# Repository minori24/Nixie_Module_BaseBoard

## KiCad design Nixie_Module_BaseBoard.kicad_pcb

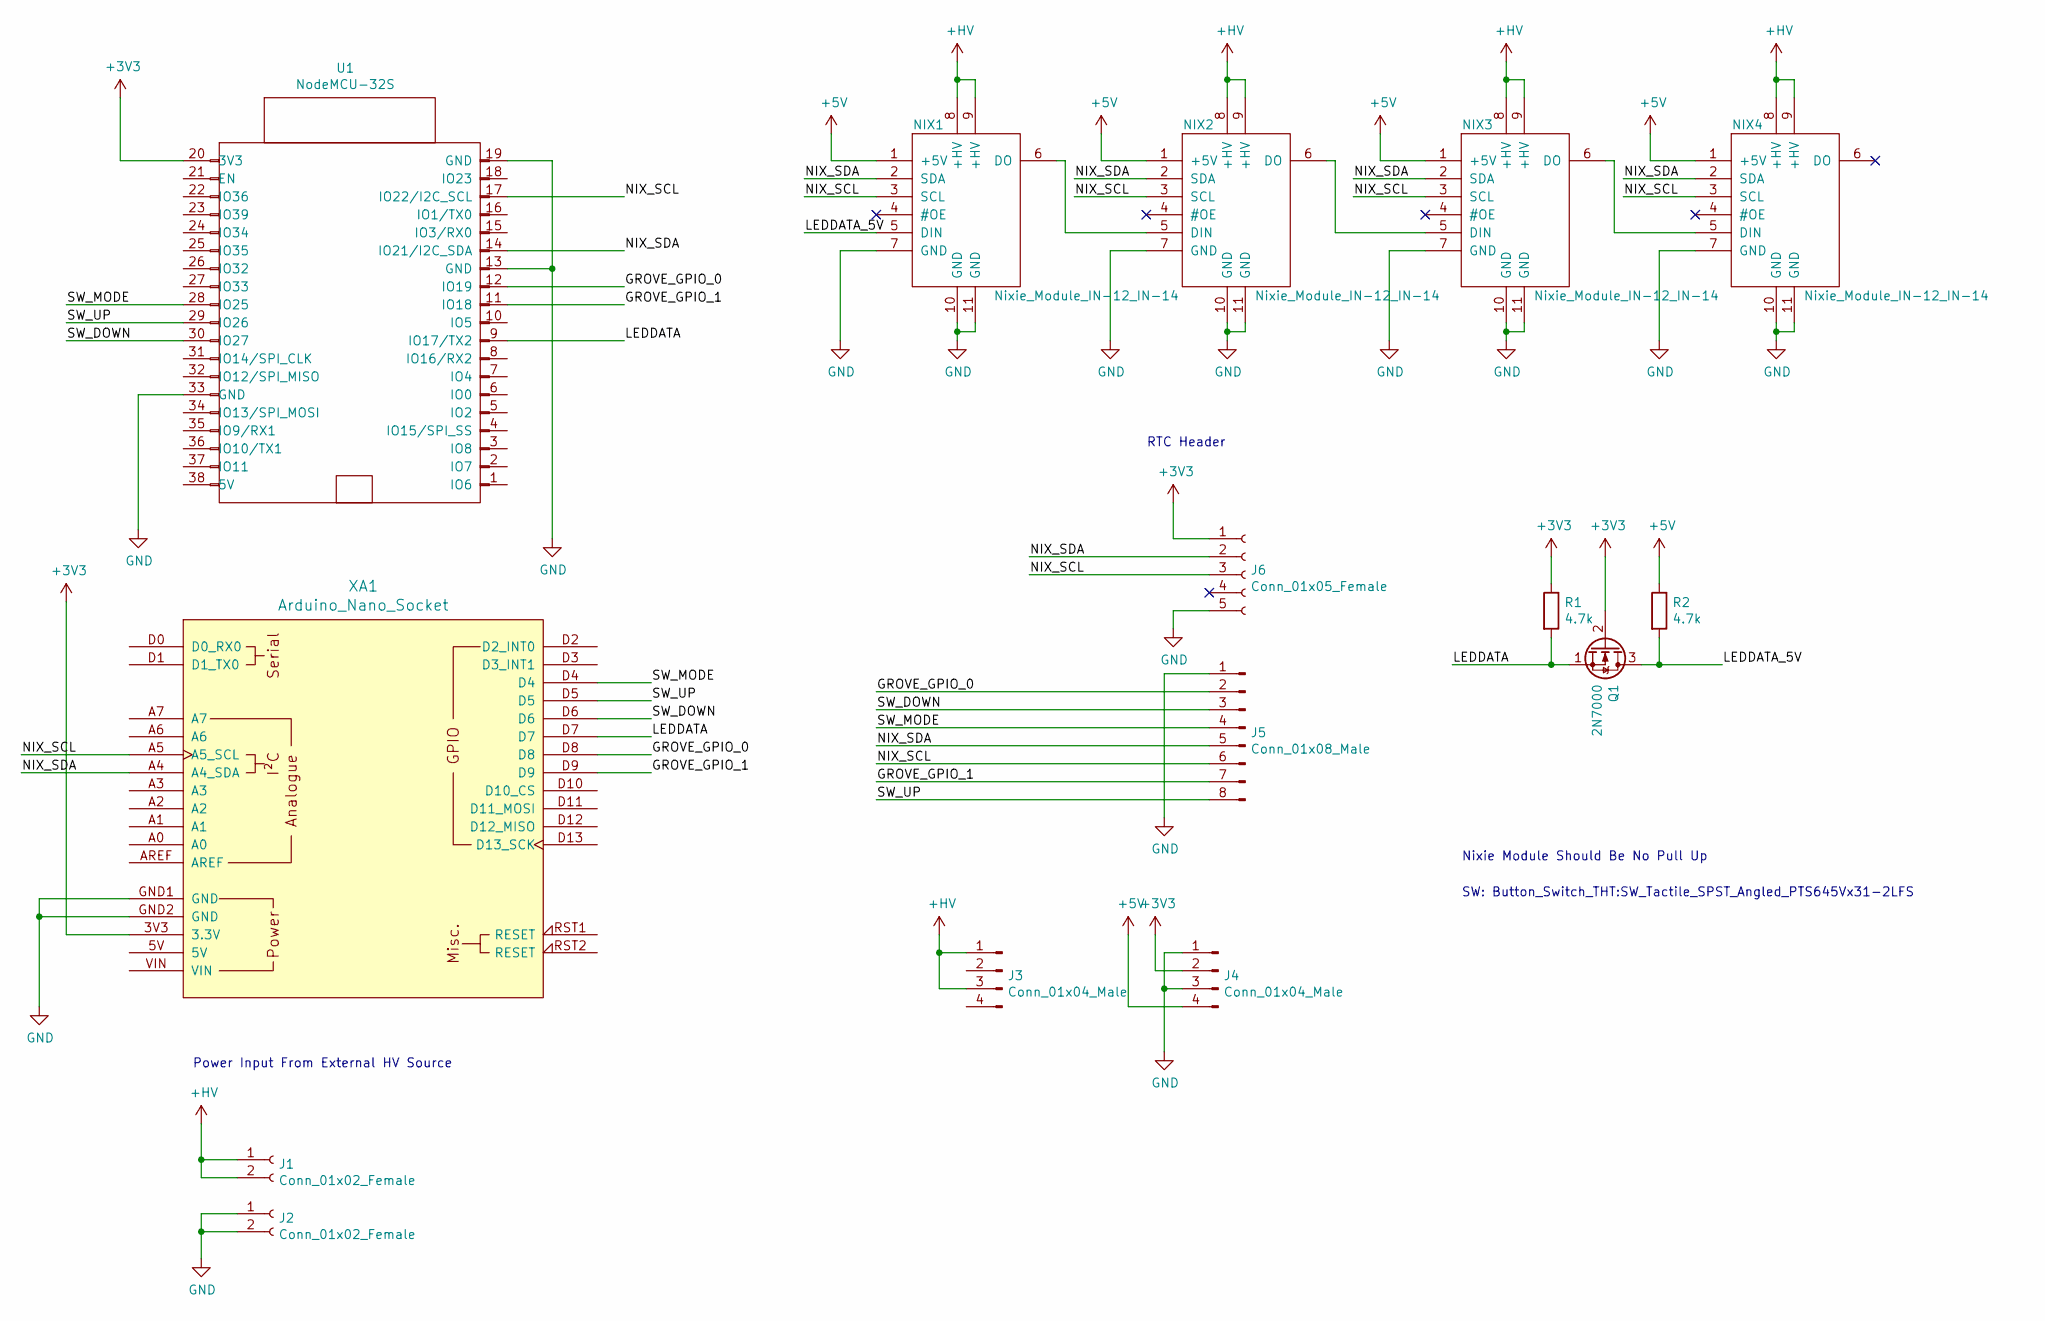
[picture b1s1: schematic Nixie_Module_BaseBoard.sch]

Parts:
J1, J2: Conn_01x02_Female; PinSocket_1x02_P2.54mm_Vertical
J3, J4: Conn_01x04_Male; PinSocket_2x02_P2.54mm_Horizontal
J5: Conn_01x08_Male; PinSocket_2x04_P2.54mm_Horizontal
J6: Conn_01x05_Female; PinSocket_1x05_P2.54mm_Vertical
NIX1, NIX2, NIX3, NIX4: Nixie_Module_IN-12_IN-14; NixieModule
Q1: 2N7000; TO-92_Wide
R1, R2: 4.7k; R_Axial_DIN0207_L6.3mm_D2.5mm_P7.62mm_Horizontal
U1: NodeMCU-32S
XA1: Arduino_Nano_Socket

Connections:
+3V3: J4.2, J6.1, Q1.2 (G), R1.1, U1.20 (3V3), XA1.3V3 (3.3V)
+5V: J4.4, NIX1.1 (+5V), NIX2.1 (+5V), NIX3.1 (+5V), NIX4.1 (+5V), R2.1
+HV: J1.1, J1.2, J3.1, J3.3, NIX1.8 (+HV), NIX1.9 (+HV), NIX2.8 (+HV), NIX2.9 (+HV), NIX3.8 (+HV), NIX3.9 (+HV), NIX4.8 (+HV), NIX4.9 (+HV)
/GROVE_GPIO_0: J5.2, U1.12 (IO19), XA1.D8
/GROVE_GPIO_1: J5.7, U1.11 (IO18), XA1.D9
/LEDDATA: Q1.1 (S), R1.2, U1.9 (IO17/TX2), XA1.D7
/LEDDATA_5V: NIX1.5 (DIN), Q1.3 (D), R2.2
/NIX_SCL: J5.6, J6.3, NIX1.3 (SCL), NIX2.3 (SCL), NIX3.3 (SCL), NIX4.3 (SCL), U1.17 (IO22/I2C_SCL), XA1.A5 (A5_SCL)
/NIX_SDA: J5.5, J6.2, NIX1.2 (SDA), NIX2.2 (SDA), NIX3.2 (SDA), NIX4.2 (SDA), U1.14 (IO21/I2C_SDA), XA1.A4 (A4_SDA)
/SW_DOWN: J5.3, U1.30 (IO27), XA1.D6
/SW_MODE: J5.4, U1.28 (IO25), XA1.D4
/SW_UP: J5.8, U1.29 (IO26), XA1.D5
GND: J2.1, J2.2, J4.1, J4.3, J5.1, J6.5, NIX1.7 (GND), NIX1.10 (GND), NIX1.11 (GND), NIX2.7 (GND), NIX2.10 (GND), NIX2.11 (GND), NIX3.7 (GND), NIX3.10 (GND), NIX3.11 (GND), NIX4.7 (GND), NIX4.10 (GND), NIX4.11 (GND), U1.13 (GND), U1.19 (GND), U1.33 (GND), XA1.GND1 (GND), XA1.GND2 (GND)
unnamed: NIX1.6 (DO), NIX2.5 (DIN)
unnamed: NIX2.6 (DO), NIX3.5 (DIN)
unnamed: NIX3.6 (DO), NIX4.5 (DIN)

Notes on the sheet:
Nixie Module Should Be No Pull Up
SW: Button_Switch_THT:SW_Tactile_SPST_Angled_PTS645Vx31-2LFS
Power Input From External HV Source
RTC Header

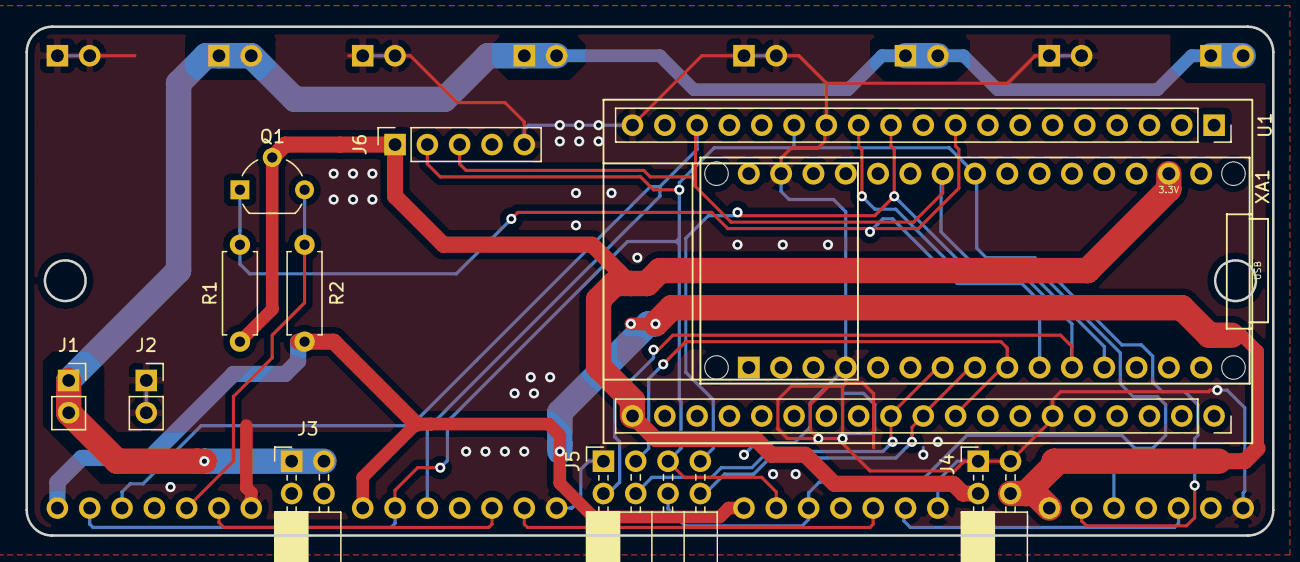
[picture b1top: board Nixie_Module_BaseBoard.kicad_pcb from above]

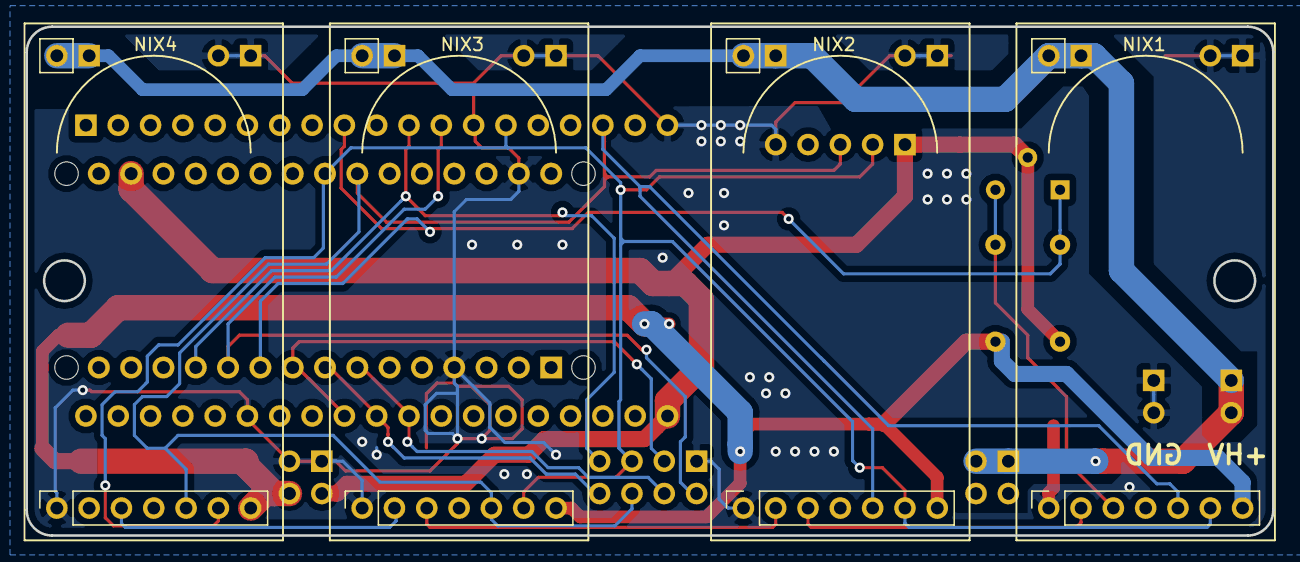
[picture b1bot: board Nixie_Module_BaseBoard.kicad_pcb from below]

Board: 2 copper layers, 98.0 x 40.0 mm, 15 parts (4 on the bottom side), 16 nets.

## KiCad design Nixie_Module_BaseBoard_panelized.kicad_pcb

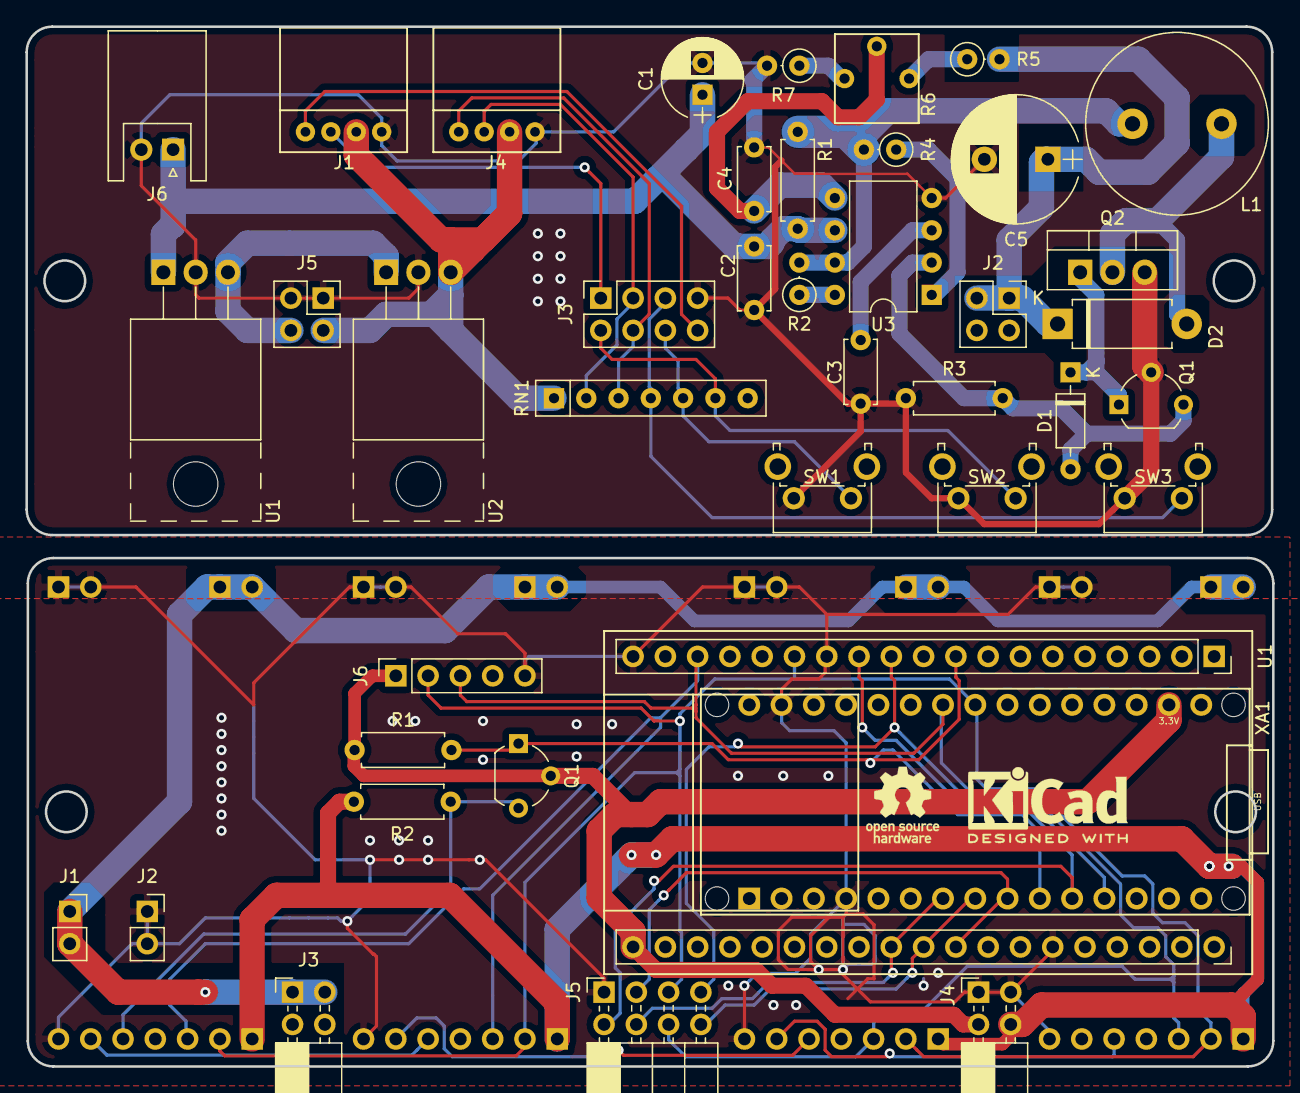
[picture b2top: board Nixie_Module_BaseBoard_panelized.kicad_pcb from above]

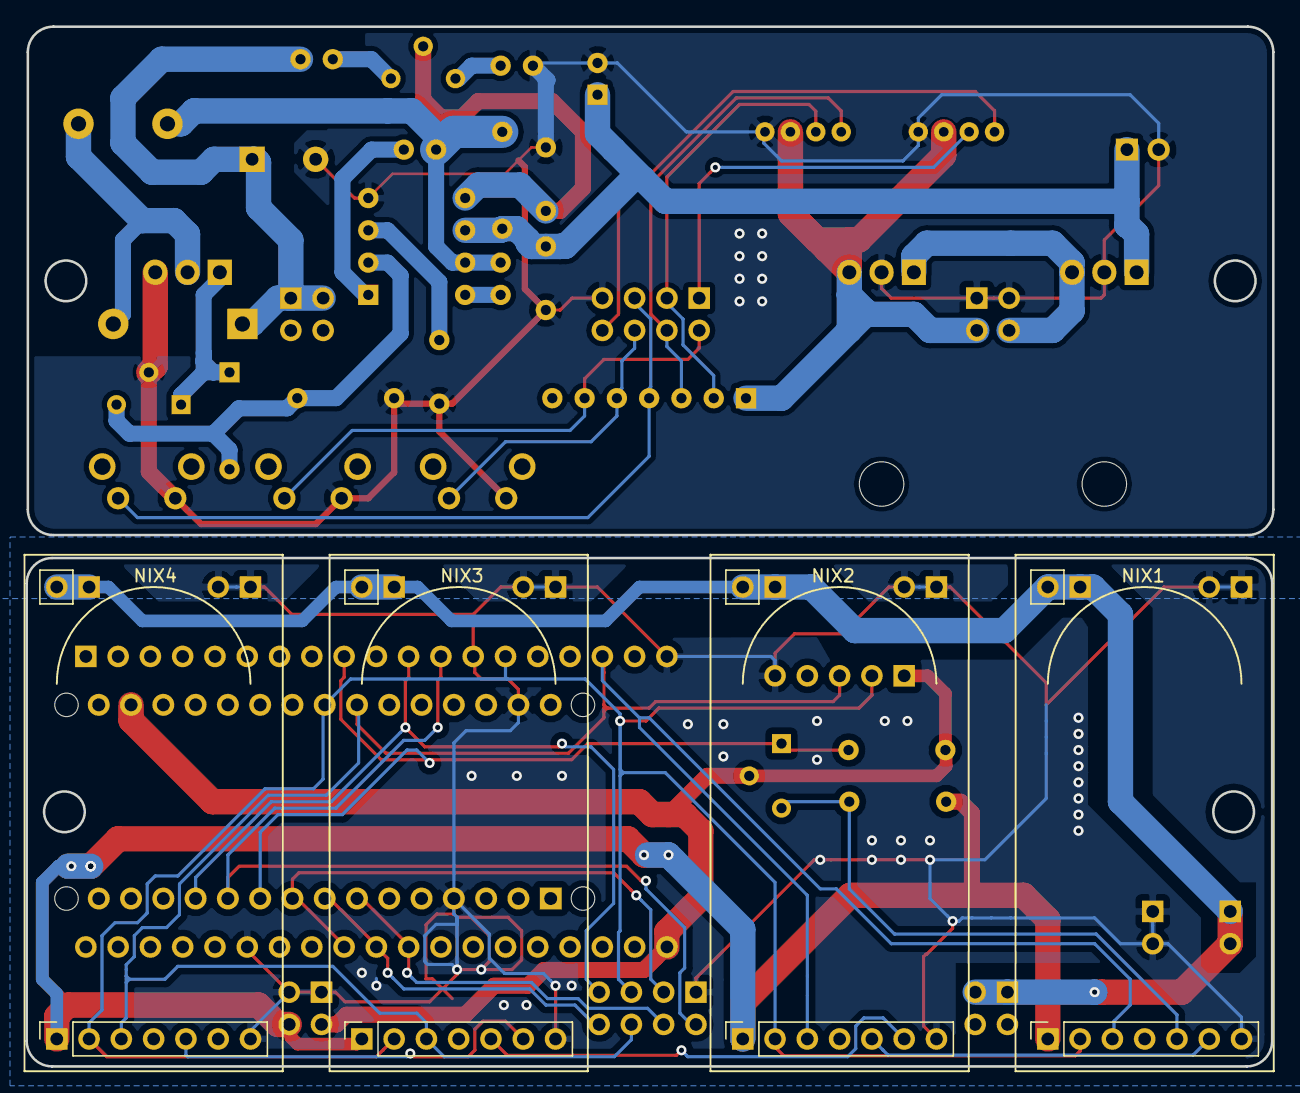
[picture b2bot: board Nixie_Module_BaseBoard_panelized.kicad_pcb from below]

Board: 2 copper layers, 98.1 x 81.8 mm, 45 parts (4 on the bottom side), 27 nets.

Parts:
C1: 100uF_16V; CP_Radial_D6.3mm_P2.50mm
C2, C4: 0.1uF; C_Disc_D5.0mm_W2.5mm_P5.00mm
C3: 1000pF; C_Disc_D5.0mm_W2.5mm_P5.00mm
C5: 4.7u_400V; CP_Radial_D10.0mm_P5.00mm
D1: 1N4148; D_DO-35_SOD27_P7.62mm_Horizontal
D2: UF2010; D_DO-15_P10.16mm_Horizontal
J1, J2: Conn_01x02_Female; PinSocket_1x02_P2.54mm_Vertical
J1#2: Grove_GPIO; Grove_THT
J2#2, J5#2: Conn_01x04_Female; PinSocket_2x02_P2.54mm_Vertical
J3, J4: Conn_01x04_Male; PinSocket_2x02_P2.54mm_Horizontal
J3#2: Conn_01x08_Female; PinSocket_2x04_P2.54mm_Vertical
J4#2: Grove_Analog; Grove_THT
J5: Conn_01x08_Male; PinSocket_2x04_P2.54mm_Horizontal
J6: Conn_01x05_Female; PinSocket_1x05_P2.54mm_Vertical
J6#2: Conn_01x02_Female; JST_XH_S02B-XH-A_02x2.50mm_Angled
L1: 470uH; Inductors_LHL13NB471K
NIX1, NIX2, NIX3, NIX4: Nixie_Module_IN-12_IN-14; NixieModule
Q1: Q_NMOS_SGD; TO-92_Wide
Q1#2: 2SA1015; TO-92_Wide
Q2: 2SK3115; TO-220-3_Vertical
R1, R2: 4.7k; R_Axial_DIN0207_L6.3mm_D2.5mm_P7.62mm_Horizontal
R1#2: 0.15; R_Axial_DIN0207_L6.3mm_D2.5mm_P7.62mm_Horizontal
R2#2: 680; R_Axial_DIN0207_L6.3mm_D2.5mm_P2.54mm_Vertical
R3: 1k; R_Axial_DIN0207_L6.3mm_D2.5mm_P7.62mm_Horizontal
R4: 1k; R_Axial_DIN0207_L6.3mm_D2.5mm_P2.54mm_Vertical
R5: 470k; R_Axial_DIN0207_L6.3mm_D2.5mm_P2.54mm_Vertical
R6: VR_2K; VOL_3362P-1-202LF
R7: 2.2k; R_Axial_DIN0207_L6.3mm_D2.5mm_P2.54mm_Vertical
RN1: R_Network06; R_Array_SIP7
SW1, SW2, SW3: SW_Push; SW_Tactile_SPST_Angled_PTS645Vx31-2LFS
U1: NodeMCU-32S
U1#2, U2: NJM7805S; TO-220-3_Horizontal_TabUp
U3: MC34063A; DIP-8_W7.62mm
XA1: Arduino_Nano_Socket

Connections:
+3V3: J1#2.3, J4.2, J4#2.3, J5#2.3, J6.1, Q1.2, R1.1, RN1.1, U1.20, U2.3, XA1.3V3
+5V: J4.4, J5#2.4, NIX1.1, NIX2.1, NIX3.1, NIX4.1, R2.1, U1#2.3, U2.1
+12V: C1.1, C2.1, J6#2.1, R1#2.2, U1#2.1, U3.6
+HV: C5.1, D2.1, J1.1, J1.2, J2#2.1, J2#2.2, J3.1, J3.3, NIX1.8, NIX1.9, NIX2.8, NIX2.9, NIX3.8, NIX3.9, NIX4.8, NIX4.9, R5.2
/GROVE_GPIO_0: J1#2.1, J3#2.8, J5.2, U1.12, XA1.D8
/GROVE_GPIO_1: J1#2.2, J3#2.1, J5.7, U1.11, XA1.D9
/LEDDATA: Q1.1, R1.2, U1.9, XA1.D7
/LEDDATA_5V: NIX1.5, Q1.3, R2.2
/NIX_SCL: J3#2.4, J4#2.1, J5.6, J6.3, NIX1.3, NIX2.3, NIX3.3, NIX4.3, RN1.3, U1.17, XA1.A5
/NIX_SDA: J3#2.3, J4#2.2, J5.5, J6.2, NIX1.2, NIX2.2, NIX3.2, NIX4.2, RN1.2, U1.14, XA1.A4
/SW_DOWN: J3#2.5, J5.3, RN1.4, SW3.1, U1.30, XA1.D6
/SW_MODE: J3#2.6, J5.4, RN1.5, SW1.1, U1.28, XA1.D4
/SW_UP: J3#2.2, J5.8, RN1.6, SW2.1, U1.29, XA1.D5
GND: C1.2, C2.2, C3.2, C4.2, C5.2, J1#2.4, J2.1, J2.2, J3#2.7, J4.1, J4.3, J4#2.4, J5.1, J5#2.1, J5#2.2, J6.5, J6#2.2, NIX1.7, NIX1.10, NIX1.11, NIX2.7, NIX2.10, NIX2.11, NIX3.7, NIX3.10, NIX3.11, NIX4.7, NIX4.10, NIX4.11, Q1#2.2, Q2.3, R3.1, R7.2, SW1.2, SW2.2, SW3.2, U1.13, U1.19, U1.33, U1#2.2, U2.2, U3.4, XA1.GND1, XA1.GND2
unnamed: C3.1, U3.3
unnamed: C4.1, R6.2, U3.5
unnamed: D1.1, Q1#2.1, Q2.1
unnamed: D1.2, Q1#2.3, R3.2, U3.2
unnamed: D2.2, L1.2, Q2.2
unnamed: L1.1, R1#2.1, R2#2.2, R4.2, U3.7
unnamed: NIX1.6, NIX2.5
unnamed: NIX2.6, NIX3.5
unnamed: NIX3.6, NIX4.5
unnamed: R2#2.1, U3.8
unnamed: R4.1, U3.1
unnamed: R5.1, R6.1
unnamed: R6.3, R7.1
